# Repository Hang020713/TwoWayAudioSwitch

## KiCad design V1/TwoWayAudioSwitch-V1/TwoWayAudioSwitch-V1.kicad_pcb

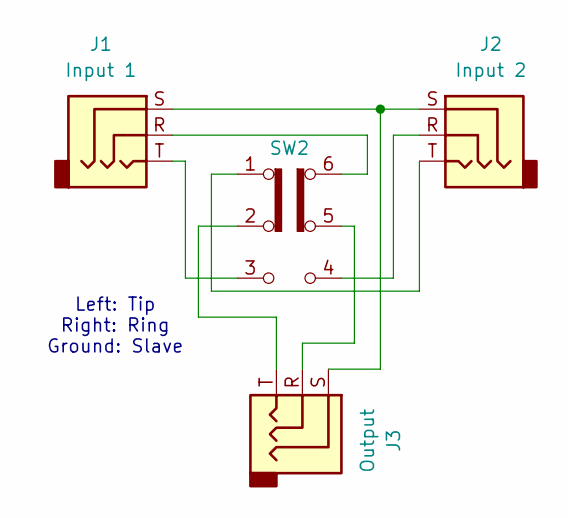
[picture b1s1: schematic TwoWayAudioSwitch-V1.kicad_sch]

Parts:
J1: Input 1; Jack_3.5mm_CUI_SJ-3523-SMT_Horizontal
J2: Input 2; Jack_3.5mm_CUI_SJ-3523-SMT_Horizontal
J3: Output; Jack_3.5mm_CUI_SJ-3523-SMT_Horizontal
SW2: SW_Slide_DPDT; SW_Push_2P2T_Toggle_CK_PVA2OAH5xxxxxxV2

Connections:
unnamed: J1.R, SW2.6 (C)
unnamed: J1.S, J2.S, J3.S
unnamed: J1.T, SW2.3 (C)
unnamed: J2.R, SW2.4 (A)
unnamed: J2.T, SW2.1 (A)
unnamed: J3.R, SW2.5 (B)
unnamed: J3.T, SW2.2 (B)

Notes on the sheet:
Left: Tip Right: Ring Ground: Slave

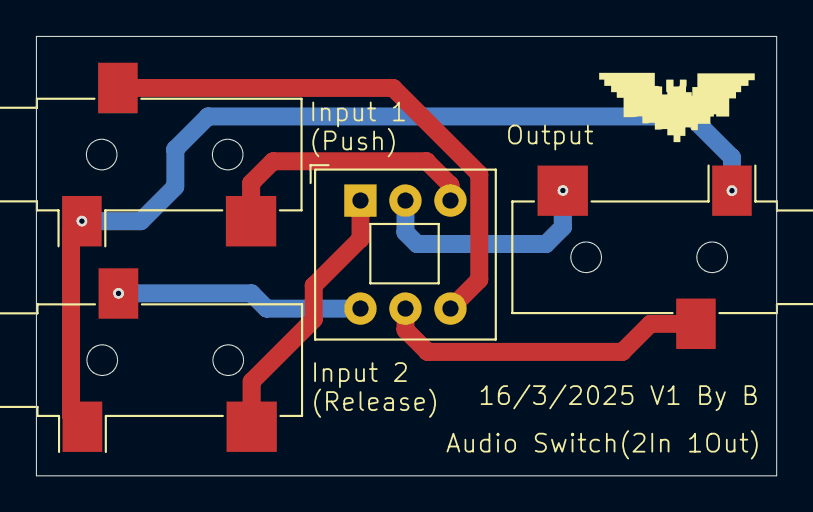
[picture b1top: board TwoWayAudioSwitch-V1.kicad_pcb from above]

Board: 2 copper layers, 41.1 x 24.4 mm, 4 parts (0 on the bottom side), 7 nets.

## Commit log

2025-03-23 Update V1
